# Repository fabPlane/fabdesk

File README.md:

# fabPlane

Desktop AI PCB generator for macOS, Linux and Windows. Sketch a board or describe it; a coding
agent (Claude Code, Codex, Cursor, Grok) drives fabPlane's MCP tools to write a
netlist (`circuit.netlist.json`), build it into a KiCad board on the FabPlane PCB design server, route it with live progress,
and verify it locally (DRC, ERC, SPICE, renders).

fabPlane runs standalone or as an MCP server inside Claude Code / Codex / Cursor / Grok.

## Layout

| Path                   | What                                                                                                                                                                                                                                      |
| ---------------------- | ----------------------------------------------------------------------------------------------------------------------------------------------------------------------------------------------------------------------------------------- |
| `apps/core`            | `fabdesk-core`: Bun daemon (compiled sidecar). Talks to the FabPlane PCB bridge (compile + routing on `kicad-cli api-server`), runs the KiCad CLI for DRC/render/export, and hosts the MCP server.                                        |
| `apps/desktop`         | Electron shell (electron-vite + React). Thin client over `fabdesk-core`.                                                                                                                                                                  |
| `apps/mobile`          | **Experimental** Expo client for iOS/Android. Pairs with a `fabdesk-core` over a tailnet. Own lockfile, not a root workspace — see [docs/mobile.md](docs/mobile.md) and [docs/mobile-testing-handoff.md](docs/mobile-testing-handoff.md). |
| `packages/protocol`    | Shared zod schemas: control API, event stream, route frames, handshake.                                                                                                                                                                   |
| `packages/tools`       | Tool registry (single source of truth) + MCP / HTTP / WebMCP / AGENTS.md adapters.                                                                                                                                                        |
| `packages/kicad`       | `kicad-cli` wrappers: DRC/ERC gate, renders, SVG, exports (local CLI helpers).                                                                                                                                                   |
| `packages/sim`         | SPICE netlist + spicey / ngspice.                                                                                                                                                                                                         |
| `packages/agents`      | Agent adapters: Claude, Codex, Cursor, Grok, [Google Antigravity](docs/antigravity.md).                                                                                                                                                                                              |
| `packages/auth-client` | fabplane.com device-code login, credential store, local mode.                                                                                                                                                                             |
| `packages/client-core` | Platform-agnostic client: `CoreClient`, the event reducer, query hooks, stores, transports. Shared by the desktop and the mobile app.                                                                                                     |
| `packages/ui`          | React components: chat, board panel, route cinema, sketch pad.                                                                                                                                                                            |
| `vendor/fab_pcb`       | git submodule → `fabPlane/fab_pcb` (FabPlane PCB). `packages/{proto,client}` are consumed as workspaces; the bridge runs as its own process.                                                                                              |

## Setup

Requires Bun 1.4.x and Node 22 (Electron tooling). Desktop installers bundle the FabPlane KiCad
fork from the rolling [`nightly` release](https://github.com/TensorFleet/kicad/releases/tag/nightly)
on [`TensorFleet/kicad`](https://github.com/TensorFleet/kicad) (`Resources/kicad/`). Leave Settings →
kicad-cli blank to use it, or set `Settings.kicadCliPath` / `KICAD_CLI` to override. Dev builds
without a staged release still fall back to `PATH` / stock installs.

```bash
git clone --recurse-submodules https://github.com/fabPlane/fabdesk.git
cd fabdesk
bun install
bun run typecheck
bun run test
bun run dev
```

Projects use `FABDESK_PROJECTS_DIR` when set. Otherwise, existing `~/Fabdesk` or `~/fabdesk`
workspaces are preserved, except when that directory is a Fabdesk source checkout. New workspaces
use `~/Fabdesk Projects`, keeping project files separate from a conventional `~/fabdesk` clone.
The daemon and desktop PCB/CAD bridges use the same directory resolver; no existing files are moved.

`bun run dev` starts **fabPlane Dev**, an isolated Electron identity (separate userData, single-instance
lock, core home and port) so it can run at the same time as an installed production fabPlane. See
[docs/dev-loop.md](docs/dev-loop.md).

Rules:

- Install dependencies from this repository root. The root lockfile also owns its public workspace dependencies; do not install inside submodules.
- Source builds and pull-request checks require no TensorFleet membership, private backend checkout, or deployment credentials.
- `circuit_build` and `route_run` need a running FabPlane PCB bridge (`bun run --filter @fp-pcb/bridge start` in a `fab_pcb` checkout with the fork `kicad-cli`); set `FABDESK_FP_PCB_BRIDGE_URL` when it is not on `http://127.0.0.1:4020`.

## Error reporting

Crash and error reports go to Sentry only when a DSN is configured (`SENTRY_DESKTOP_DSN` at runtime, or the
`SENTRY_DESKTOP_DSN` repo secret baked into release builds); development builds send nothing. Users can opt
out in Settings → Privacy. Reports never include prompts, board files, tokens or project paths. See
[docs/sentry.md](docs/sentry.md).

The onboarding drop-off funnel is a separate, optional PostHog capture from `fabdesk-core` (no SDK).
It is off unless `POSTHOG_KEY` is set; users can also turn it off in Settings → Privacy. Events never
include prompts, board files, tokens, emails, project names or paths. See
[docs/onboarding-funnel.md](docs/onboarding-funnel.md).

Agent-run debugging is separate from crash reporting: every in-app run gets a portable `llm-dump.json`
with its ordered agent/MCP/KiCad timeline and pre-tool project snapshots. Complete dumps are also kept
in Fabdesk's existing SQLite database for simple lookup and export, with no extra service required. See
[docs/agent-run-telemetry.md](docs/agent-run-telemetry.md).

## Auth

fabPlane signs in through fabplane.com using the OAuth device-authorization flow. For local
development set `FABDESK_AUTH_MODE=local` (honored only in non-public channels or with a
`.fabdesk-dev` marker in the fabPlane config dir).

Backend handoff (running the daemon against the FabPlane PCB bridge, CI keys, open work): [docs/handoff-fab-pcb.md](docs/handoff-fab-pcb.md).

Final cross-repository PR stack, merge order, issue mapping, and Linux packaging evidence: [docs/final-pcb-pr-stack-handoff.md](docs/final-pcb-pr-stack-handoff.md).

`kicad_stats` additionally requires the optional `kicad-cli pcb export stats` command.
Some stock and packaged KiCad builds omit it, regardless of version. `doctor` probes
the command and reports when board statistics are unavailable; other supported exports,
DRC and rendering remain usable.

## CI Linux runners

Trusted Linux workflows pick the repository NAS runner by default. Set the Actions
variable `FORCE_BLACKSMITH_LINUX=true` (or `LINUX_RUNNER=blacksmith`) to pin Blacksmith
until it is unset. A short `NAS_RUNNER_OUTAGE_UNTIL` lease still covers brief outages.
See [docs/ci-runner-policy.md](docs/ci-runner-policy.md).

## Contributing and security

See [CONTRIBUTING.md](CONTRIBUTING.md) for local checks and pull requests and
[SECURITY.md](SECURITY.md) for private vulnerability reporting. Bundled engines,
routers, libraries and artwork keep their own licenses; see
[THIRD_PARTY_NOTICES.md](THIRD_PARTY_NOTICES.md).

The mobile app is experimental. Signed installers, Apple notarization and hosted
sharing are separate from building the source. Current migration/release limits
are recorded in [docs/fabplane-repository-cutover.md](docs/fabplane-repository-cutover.md).

## License

Original FabDesk source in this repository is licensed under [Apache-2.0](LICENSE).
Submodule repositories and third-party components are outside that grant and
retain their own terms; see [THIRD_PARTY_NOTICES.md](THIRD_PARTY_NOTICES.md).

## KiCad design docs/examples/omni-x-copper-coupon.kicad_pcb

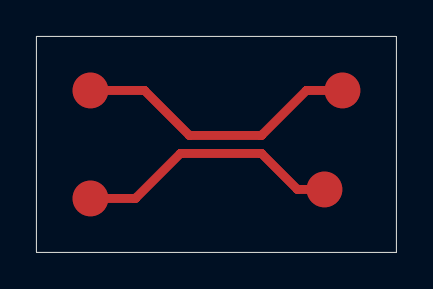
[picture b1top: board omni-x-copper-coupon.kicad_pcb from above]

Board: 2 copper layers, 20.0 x 12.0 mm, 4 parts (0 on the bottom side), 2 nets.

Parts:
TP1, TP2: NET_A; CouponProbe
TP3, TP4: NET_B; CouponProbe

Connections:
NET_A: TP1.1, TP2.1
NET_B: TP3.1, TP4.1

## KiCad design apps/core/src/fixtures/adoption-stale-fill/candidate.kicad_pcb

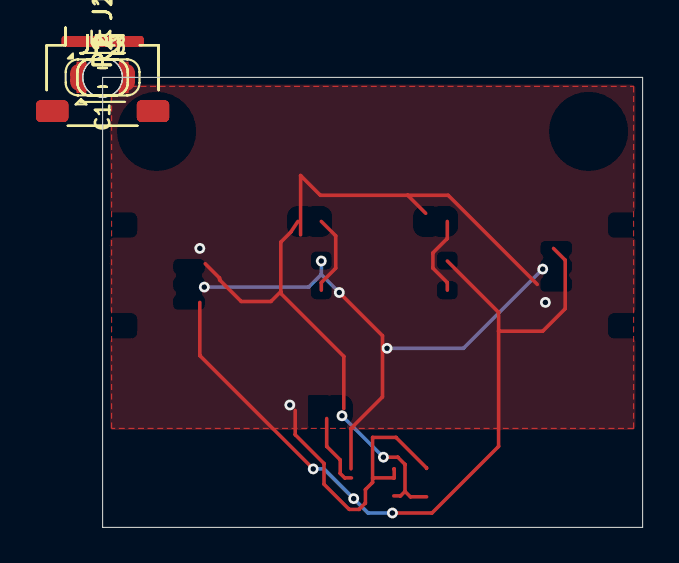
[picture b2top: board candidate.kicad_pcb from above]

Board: 2 copper layers, 30.0 x 25.0 mm, 11 parts (0 on the bottom side), 7 nets.

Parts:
C1: 100nF; C_0603_1608Metric
H1, H2: M2 NPTH; MountingHole_2.2mm_M2
J1, J2: SM04B-SRSS-TB; JST_SH_SM04B-SRSS-TB_1x04-1MP_P1.00mm_Horizontal
JP1, JP2: CUT TO DISABLE; SolderJumper-2_P1.3mm_Bridged_RoundedPad1.0x1.5mm
JP3: ADDR 44 / 45; SolderJumper-3_P1.3mm_Bridged12_RoundedPad1.0x1.5mm
R1, R2: 4.7k; R_0603_1608Metric
U1: SHT31-DIS-B; Sensirion_DFN-8-1EP_2.5x2.5mm_P0.5mm_EP1.1x1.7mm

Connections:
3V3: C1.1, J1.2, J2.2, JP1.1 (A), JP2.1 (A), JP3.3 (B), U1.5 (VDD)
ADDR: JP3.2 (C), U1.2 (ADDR)
GND: C1.2, J1.1, J2.1, JP3.1 (A), U1.7 (R), U1.8 (VSS), U1.9 (VSS)
PU_SCL: JP2.2 (B), R2.1
PU_SDA: JP1.2 (B), R1.1
SCL: J1.4, J2.4, R2.2, U1.4 (SCL)
SDA: J1.3, J2.3, R1.2, U1.1 (SDA)

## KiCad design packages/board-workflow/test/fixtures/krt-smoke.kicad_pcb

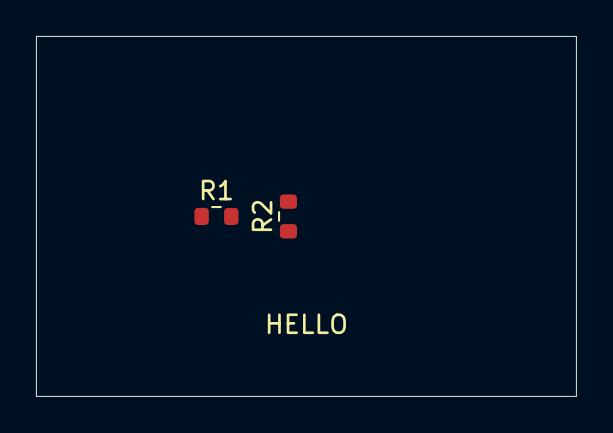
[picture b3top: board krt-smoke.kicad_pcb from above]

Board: 2 copper layers, 30.0 x 20.0 mm, 3 parts (1 on the bottom side), 2 nets, no tracks yet.

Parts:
R1, R2, R3: 10k; R_0603_1608Metric

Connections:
A: R1.1, R2.1, R3.1
B: R1.2, R2.2, R3.2

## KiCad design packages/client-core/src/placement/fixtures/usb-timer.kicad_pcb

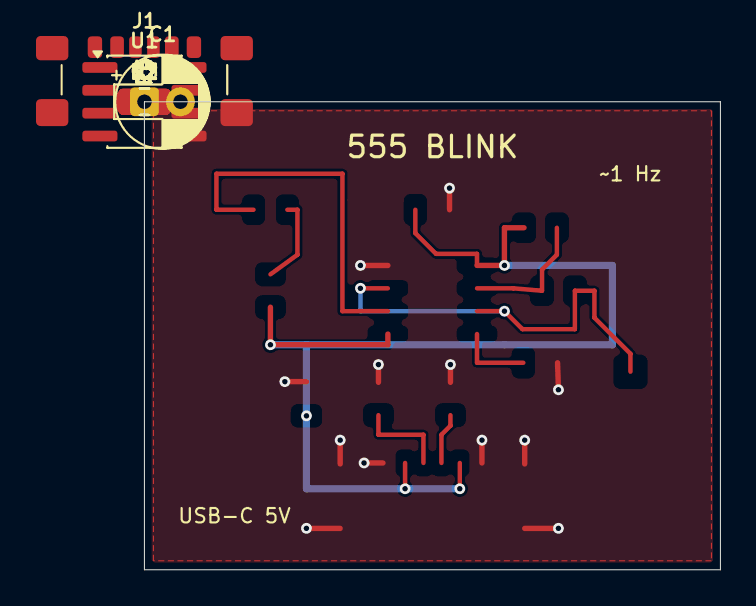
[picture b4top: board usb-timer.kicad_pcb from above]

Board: 2 copper layers, 32.0 x 26.0 mm, 12 parts (0 on the bottom side), 9 nets.

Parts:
C1: 10u 16V; CP_Radial_D5.0mm_P2.00mm
C2: 10n 50V; C_0805_2012Metric
C3: 100n 50V; C_0805_2012Metric
C4: 1u 16V X7R; C_0805_2012Metric
D1: Red; LED_0805_2012Metric
J1: USB4135-GF-A; USB_C_Receptacle_GCT_USB4135-GF-A_6P_TopMnt_Horizontal
R1: 4.7k 1%; R_0805_2012Metric
R2: 68k 1%; R_0805_2012Metric
R3, R4: 5.1k 1%; R_0805_2012Metric
R5: 1k; R_0805_2012Metric
U1: TLC555ID; SOIC-8_3.9x4.9mm_P1.27mm

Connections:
/CC1: J1.A5 (CC1), R3.1
/CC2: J1.B5 (CC2), R4.1
/CONTROL: C2.1, U1.5 (CONT)
/DISCH: R1.2, R2.1, U1.7 (DISCH)
/GND: C1.2, C2.2, C3.2, C4.2, J1.A12 (GND), J1.B12 (GND), J1.S1 (SHIELD), R3.2, R4.2, U1.1 (GND)
/LED_A: D1.2 (A), R5.2
/OUT: D1.1 (K), U1.3 (OUT)
/TIMING: C1.1, R2.2, U1.2 (TRIG), U1.6 (THRES)
/VBUS: C3.1, C4.1, J1.A9 (VBUS), J1.B9 (VBUS), R1.1, R5.1, U1.4 (~RST), U1.8 (VCC)
